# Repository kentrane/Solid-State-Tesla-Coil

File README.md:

# Solid State Tesla Coil Driver Board
 Tesla coil design for fun and danger, but mostly fun
## Introduction
This is a design for a basic DRSSTC using an H-bridge 
## Schematic

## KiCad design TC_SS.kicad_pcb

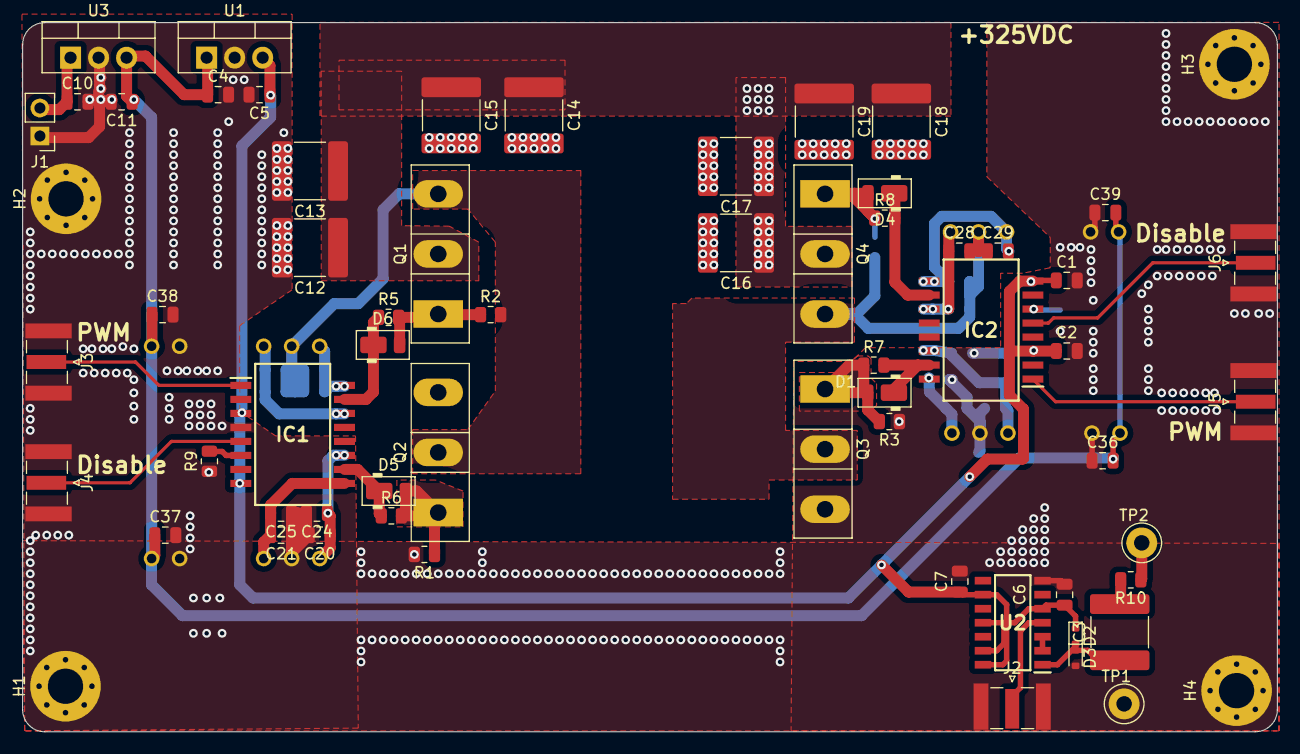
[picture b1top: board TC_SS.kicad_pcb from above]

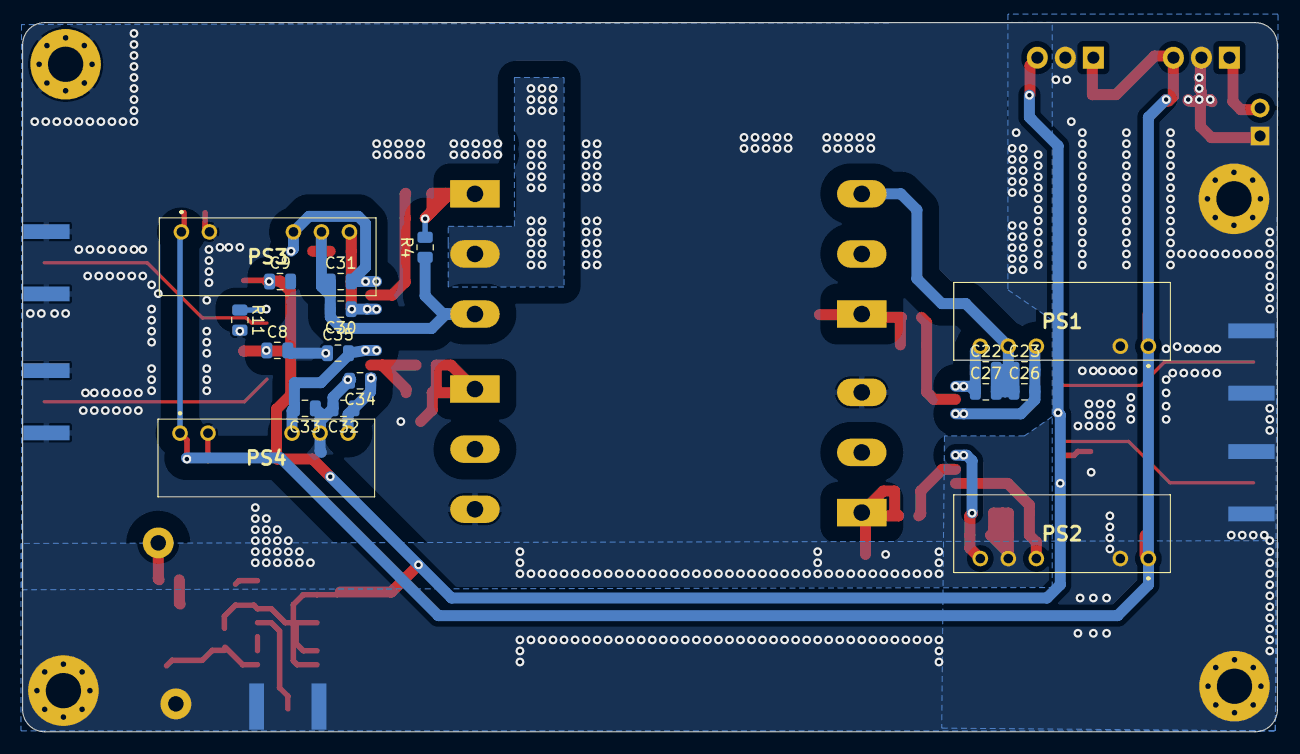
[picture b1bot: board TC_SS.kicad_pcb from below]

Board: 2 copper layers, 113.8 x 64.3 mm, 81 parts (18 on the bottom side), 34 nets.

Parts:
C1, C2, C5, C6, C7, C8, C9, C11, C20, C21, C22, C23, C28, C29, C32, C33, C36, C37, C38, C39: 1u; C_0805_2012Metric
C3, C12, C13, C14, C15, C16, C17, C18, C19: 100n; C_2220_5650Metric
C4, C10: 10u; C_0805_2012Metric
C24, C25, C26, C27, C30, C31, C34, C35: 100n; C_0805_2012Metric
D1, D4, D5, D6: DFLS120L-7; D_PowerDI-123
D2, D3: 1N4148WT; D_SOD-523
H1, H2, H3, H4: MountingHole_Pad; MountingHole_3.2mm_M3_Pad_Via
IC1, IC2: ADUM4221-1ARIZ; SOIC127P1030X264-16N
J1: 15V_In; PinHeader_1x02_P2.54mm_Vertical
J2, J3, J4, J5, J6: Conn_Coaxial; SMA_Samtec_SMA-J-P-X-ST-EM1_EdgeMount
PS1, PS2, PS3, PS4: RKZ-1215S_H; RKZ1215SH
Q1, Q2, Q3, Q4: IPW60R099P6XKSA1; TO-247-3_Vertical
R1, R2, R3, R4: 10k; R_0805_2012Metric
R5, R6, R7, R8: 22; R_0805_2012Metric
R9, R11: 4.7; R_0805_2012Metric
R10: 100; R_0805_2012Metric
TP1, TP2: TestPoint; TestPoint_Loop_D3.50mm_Drill1.4mm_Beaded
U1: LM7805_TO220; TO-220-3_Vertical
U2: 74HC14; SOIC127P600X175-14N
U3: LM7812_TO220; TO-220-3_Vertical

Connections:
+5V: C1.1, C2.1, C5.1, C6.1, C7.1, C8.1, C9.1, D2.1 (K), IC1.3 (VDD1_1), IC1.8 (VDD1_2), IC2.3 (VDD1_1), IC2.8 (VDD1_2), U1.3 (VO), U2.5, U2.9, U2.11, U2.13, U2.14 (VCC)
+12V: C4.1, C11.1, C36.2, C37.1, C38.1, C39.2, PS1.1 (+VIN), PS2.1 (+VIN), PS3.1 (+VIN), PS4.1 (+VIN), U1.1 (VI), U3.3 (VO)
/HS1_G: D6.2 (A), Q1.1 (G), R2.1, R5.2
/LS1_G: D5.2 (A), Q2.1 (G), R1.1, R6.2
GND: C1.2, C2.2, C4.2, C5.2, C6.2, C7.2, C8.2, C9.2, C10.2, C11.2, C12.2, C13.2, C14.2, C15.2, C16.2, C17.2, C18.2, C19.2, C20.2, C21.1, C24.2, C25.1, C32.2, C33.1, C34.2, C35.1, C36.1, C37.2, C38.2, C39.1, D3.2 (A), H1.1, H2.1, H3.1, H4.1, IC1.4 (GND1), J1.1, J2.2 (Ext), J3.2 (Ext), J4.2 (Ext), J5.2 (Ext), J6.2 (Ext), PS1.2 (-VIN), PS2.2 (-VIN), PS2.6 (NO_PIN), PS3.2 (-VIN), PS4.2 (-VIN), PS4.6 (NO_PIN), Q2.3 (S), Q3.3 (S), R1.2, R3.1, R9.1, R11.2, TP1.1, U1.2 (GND), U2.7 (GND), U3.2 (GND)
HB1: C22.2, C23.1, C26.1, C27.2, PS1.6 (NO_PIN), Q1.3 (S), Q2.2 (D), R2.2
HB2: C28.2, C29.1, C30.2, C31.1, PS3.6 (NO_PIN), Q3.2 (D), Q4.3 (S), R4.1
unnamed: R10.1, TP2.1
unnamed: C3.2, R10.2
unnamed: D1.2 (A), Q3.1 (G), R3.2, R7.1
unnamed: D1.1 (K), IC2.15 (VOA), R7.2
unnamed: C3.1, D2.2 (A), D3.1 (K), U2.1
unnamed: D4.2 (A), Q4.1 (G), R4.2, R8.1
unnamed: D4.1 (K), IC2.10 (VOB), R8.2
unnamed: D5.1 (K), IC1.10 (VOB), R6.1
unnamed: D6.1 (K), IC1.15 (VOA), R5.1
unnamed: IC1.5 (DISABLE), J4.1 (In)
unnamed: IC1.6 (DT), R9.2
unnamed: IC1.1 (PWM), J3.1 (In)
unnamed: IC2.5 (DISABLE), J6.1 (In)
unnamed: IC2.6 (DT), R11.1
unnamed: IC2.1 (PWM), J5.1 (In)
unnamed: C10.1, J1.2, U3.1 (VI)
unnamed: U2.2, U2.3
PWM: J2.1 (In), U2.4
VDC: C12.1, C13.1, C14.1, C15.1, C16.1, C17.1, C18.1, C19.1, Q1.2 (D), Q4.2 (D)
Vg_neg_HS1: C23.2, C26.2, IC1.14 (GNDA), PS1.5 (-VOUT)
Vg_neg_HS2: C29.2, C31.2, IC2.9 (GNDB), PS3.5 (-VOUT)
Vg_neg_LS1: C21.2, C25.2, IC1.9 (GNDB), PS2.5 (-VOUT)
Vg_neg_LS2: C33.2, C35.2, IC2.14 (GNDA), PS4.5 (-VOUT)
Vg_pos_HS1: C22.1, C27.1, IC1.16 (VDDA), PS1.7 (+VOUT)
Vg_pos_HS2: C28.1, C30.1, IC2.11 (VDDB), PS3.7 (+VOUT)
Vg_pos_LS1: C20.1, C24.1, IC1.11 (VDDB), PS2.7 (+VOUT)
Vg_pos_LS2: C32.1, C34.1, IC2.16 (VDDA), PS4.7 (+VOUT)

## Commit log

2023-11-09 Initital commit
2023-11-09 Started Schematic
2023-11-09 Removing all files in .gitignore
2023-11-12 Update README.md with preliminary component list
2023-11-12 Add some more values to components
2023-11-12 Drop files from .gitignore
2023-11-13 Add more values
2023-11-18 Update component list
2023-11-19 Update input driver
2023-11-21 Add more footprints and start board
2023-11-22 Update Power PCB
2023-11-22 Do power PCB layout
2023-11-22 add pic
2023-11-29 Update schematic
2023-11-30 Swap gate driver for Adum4221-1
2023-11-30 Update basically everything
2023-12-05 Almost ready to produce
2023-12-05 Done now (probably)
2023-12-05 Update Graphics
